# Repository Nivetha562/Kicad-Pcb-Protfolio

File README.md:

# KiCad PCB Design Portfolio

Welcome to my PCB Design Portfolio!

I am an Electronics and Communication Engineering student interested in PCB design and electronics hardware development.

## Tools Used
- KiCad
- PCB Layout Design
- Schematic Design

## My Projects

1. LED Blinker
2. PN Junction
3. Project 1.2
4. USB-C 5V Power Supply
5. Project 1.4
6. Running Light Board
7. Soil Moisture Monitoring
8. STEM Toy

## About
This repository contains my PCB design projects created using KiCad. These projects helped me improve my knowledge of electronic circuits, schematic design, and PCB layout.

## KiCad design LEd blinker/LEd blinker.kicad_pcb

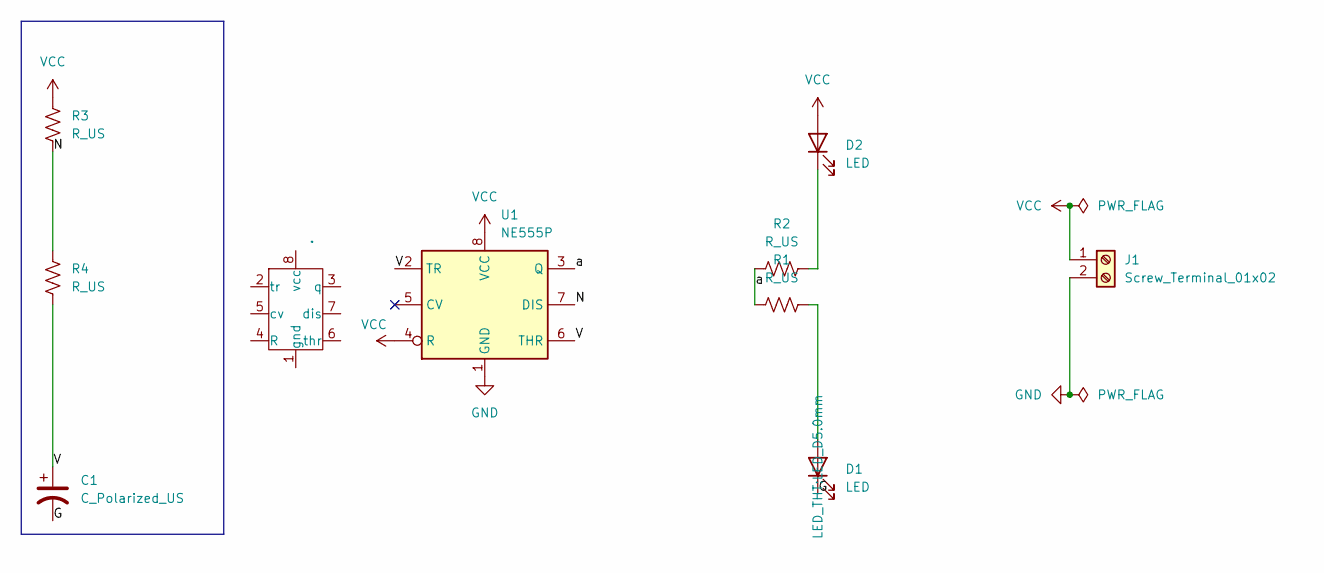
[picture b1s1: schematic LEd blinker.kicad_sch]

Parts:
C1: C_Polarized_US; CP_Axial_L11.0mm_D6.0mm_P18.00mm_Horizontal
D1, D2: LED; LED_D5.0mm
J1: Screw_Terminal_01x02; TerminalBlock_Phoenix_MKDS-1,5-2-5.08_1x02_P5.08mm_Horizont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
R1, R2: R_US; R_Axial_DIN0204_L3.6mm_D1.6mm_P7.62mm_Horizontal
R3, R4: R_US; R_Axial_DIN0207_L6.3mm_D2.5mm_P7.62mm_Horizontal
U1: NE555P; DIP-8_W7.62mm
U4: (no value)

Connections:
/G: C1.2, D1.1 (K)
/N: R3.1, R4.2, U1.7 (DIS)
/V: C1.1, R4.1, U1.2 (TR), U1.6 (THR)
/a: R1.1, R2.1, U1.3 (Q)
GND: J1.2, U1.1 (GND)
unnamed: D1.2 (A), R1.2
unnamed: D2.1 (K), R2.2
VCC: D2.2 (A), J1.1, R3.2, U1.4 (R), U1.8 (VCC)

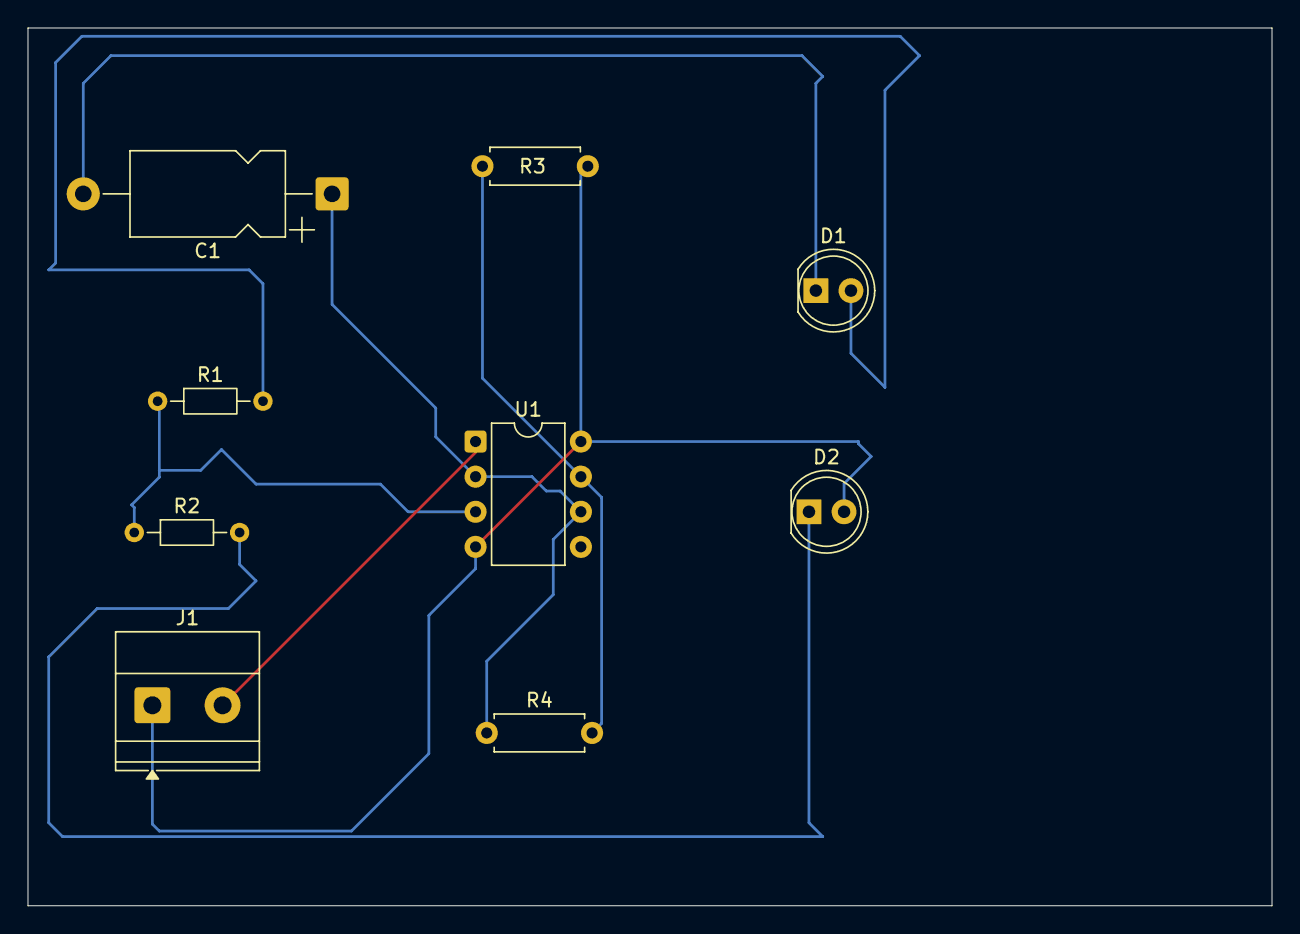
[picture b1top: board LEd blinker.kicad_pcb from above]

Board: 2 copper layers, 90.0 x 63.5 mm, 9 parts (0 on the bottom side), 8 nets.

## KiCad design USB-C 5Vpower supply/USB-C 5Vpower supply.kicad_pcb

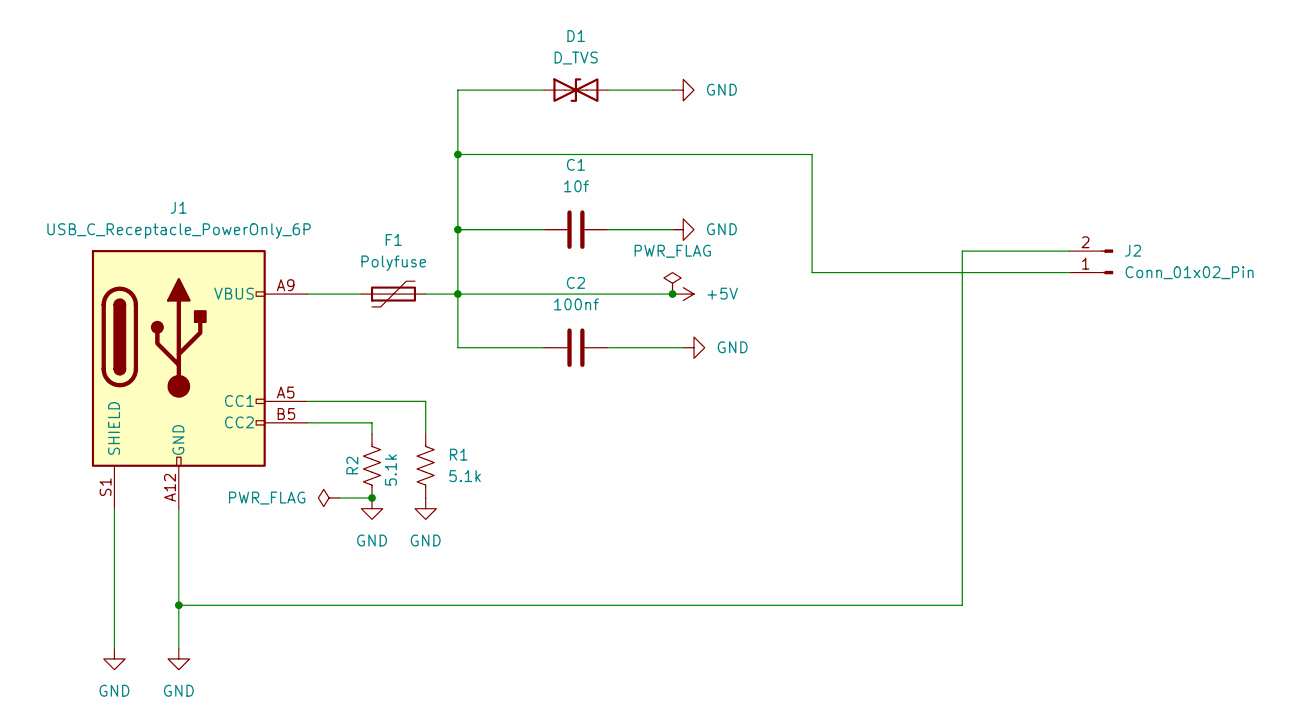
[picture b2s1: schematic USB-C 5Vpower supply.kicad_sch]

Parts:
C1: 10f; CP_Radial_D5.0mm_P2.00mm
C2: 100nf; CP_Radial_D5.0mm_P2.00mm
D1: D_TVS; D_DO-15_P5.08mm_Vertical_KathodeUp
F1: Polyfuse; Fuse_1812_4532Metric
J1: USB_C_Receptacle_PowerOnly_6P; USB_C_Receptacle_GCT_USB4125-xx-x-0190_6P_TopMnt_Horizontal
J2: Conn_01x02_Pin; SolderWire-4sqmm_1x02_P12mm_D3mm_OD6mm
R1, R2: 5.1k; R_Axial_DIN0207_L6.3mm_D2.5mm_P10.16mm_Horizontal

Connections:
+5V: C1.1, C2.1, D1.1 (A1), F1.2, J2.1
GND: C1.2, C2.2, D1.2 (A2), J1.A12 (GND), J1.B12 (GND), J1.S1 (SHIELD), J2.2, R1.2, R2.2
unnamed: F1.1, J1.A9 (VBUS), J1.B9 (VBUS)
unnamed: J1.A5 (CC1), R1.1
unnamed: J1.B5 (CC2), R2.1

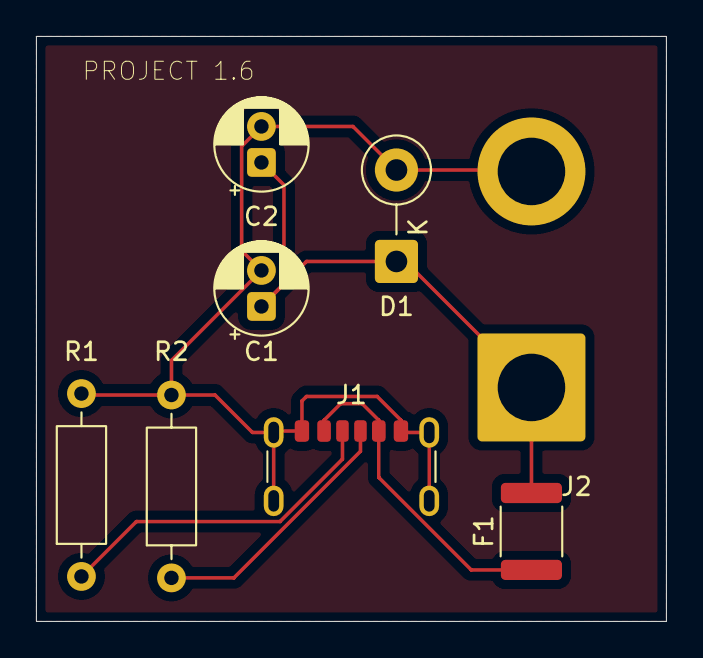
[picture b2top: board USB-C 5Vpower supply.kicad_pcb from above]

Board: 2 copper layers, 35.0 x 32.5 mm, 8 parts (0 on the bottom side), 5 nets.

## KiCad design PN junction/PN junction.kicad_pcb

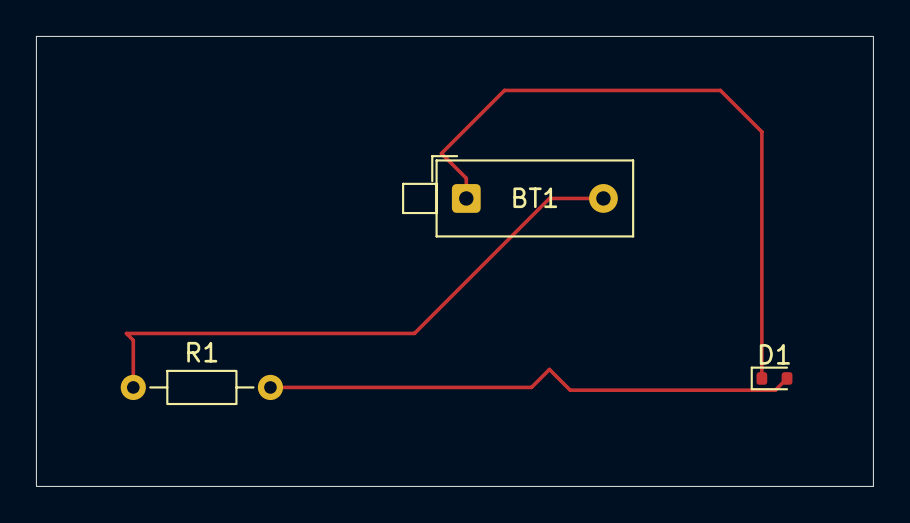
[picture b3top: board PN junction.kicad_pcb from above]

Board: 2 copper layers, 46.5 x 25.0 mm, 3 parts (0 on the bottom side), 3 nets.

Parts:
BT1: Battery_Cell; SW_DIP_SPSTx01_Piano_10.8x4.1mm_W7.62mm_P2.54mm
D1: 1N4148WT; D_SOD-523
R1: R_US; R_Axial_DIN0204_L3.6mm_D1.6mm_P7.62mm_Horizontal

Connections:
unnamed: BT1.1 (+), D1.1 (K)
unnamed: BT1.2 (-), R1.1
unnamed: D1.2 (A), R1.2

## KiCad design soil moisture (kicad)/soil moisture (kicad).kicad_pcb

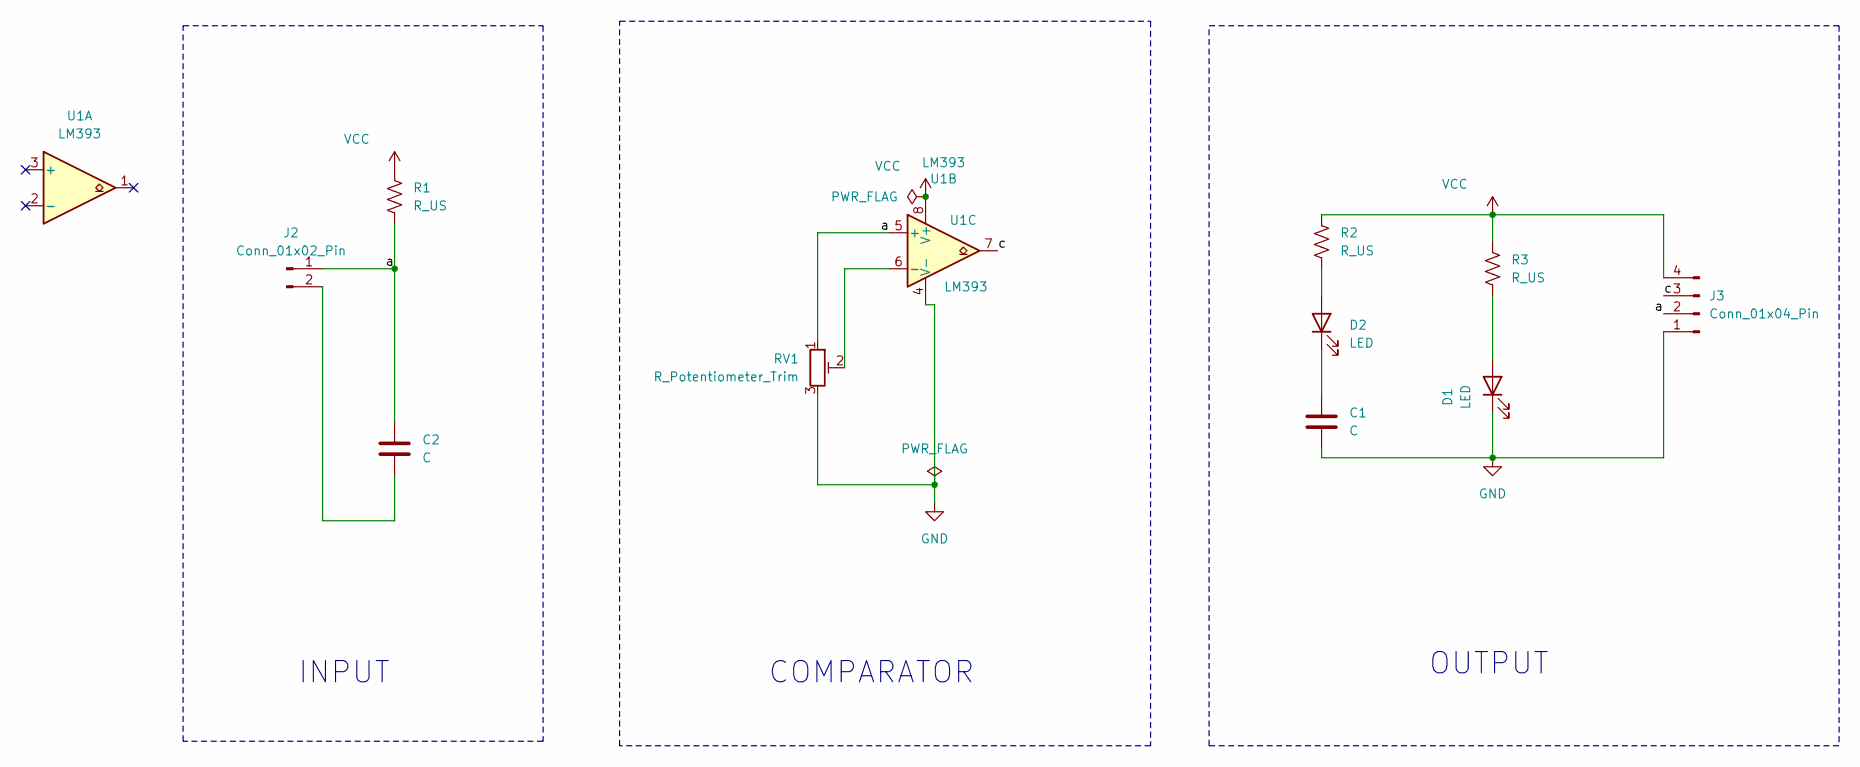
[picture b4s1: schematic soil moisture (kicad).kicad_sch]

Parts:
C1, C2: C; C_Radial_D5.0mm_H11.0mm_P2.00mm
D1, D2: LED; LED_D3.0mm_Horizontal_O1.27mm_Z2.0mm_Clear
J2: Conn_01x02_Pin; PinSocket_1x02_P2.54mm_Vertical
J3: Conn_01x04_Pin; PinSocket_1x04_P2.54mm_Vertical
R1, R2, R3: R_US; R_Axial_DIN0207_L6.3mm_D2.5mm_P15.24mm_Horizontal
RV1: R_Potentiometer_Trim; Potentiometer_Piher_PT-15-V02_Vertical
U1: LM393; DIP-8_W7.62mm

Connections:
/a: C2.1, J2.1, J3.2, R1.2, RV1.1, U1.5 (+)
/c: J3.3, U1.7
GND: C1.2, D1.1 (K), J3.1, RV1.3, U1.4 (V-)
unnamed: D1.2 (A), R3.2
unnamed: D2.2 (A), R2.2
unnamed: C1.1, D2.1 (K)
unnamed: C2.2, J2.2
unnamed: RV1.2, U1.6 (-)
VCC: J3.4, R1.1, R2.1, R3.1, U1.8 (V+)

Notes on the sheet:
OUTPUT
COMPARATOR
INPUT

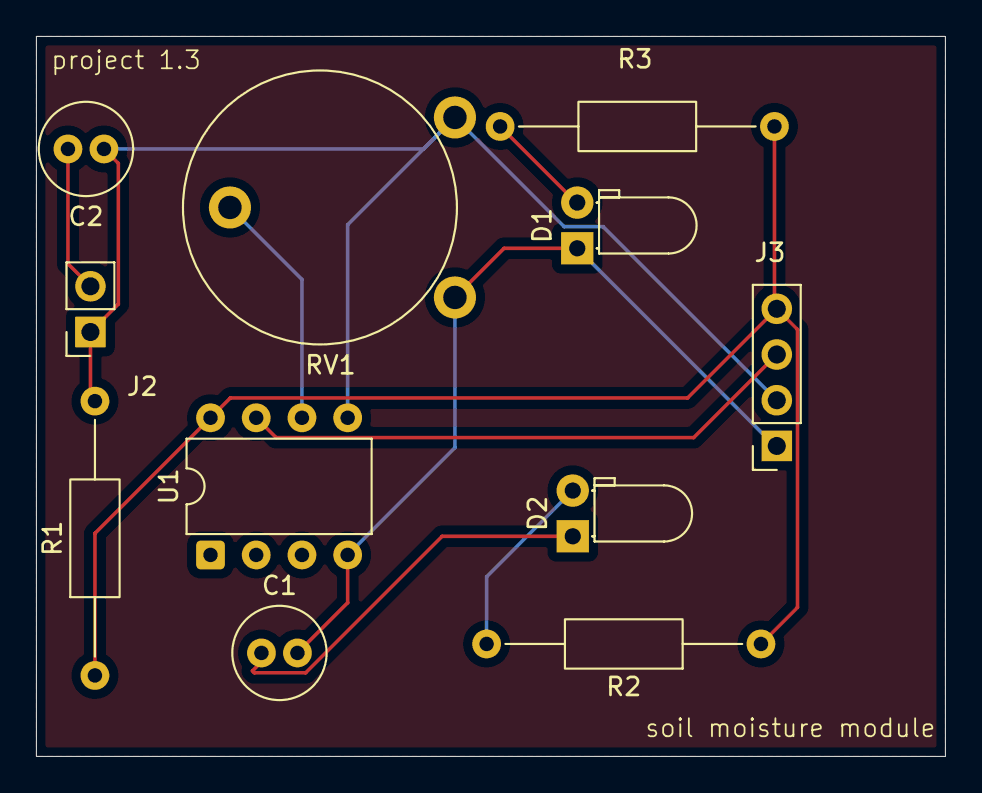
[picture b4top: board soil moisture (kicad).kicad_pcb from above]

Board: 2 copper layers, 50.5 x 40.0 mm, 11 parts (0 on the bottom side), 9 nets.

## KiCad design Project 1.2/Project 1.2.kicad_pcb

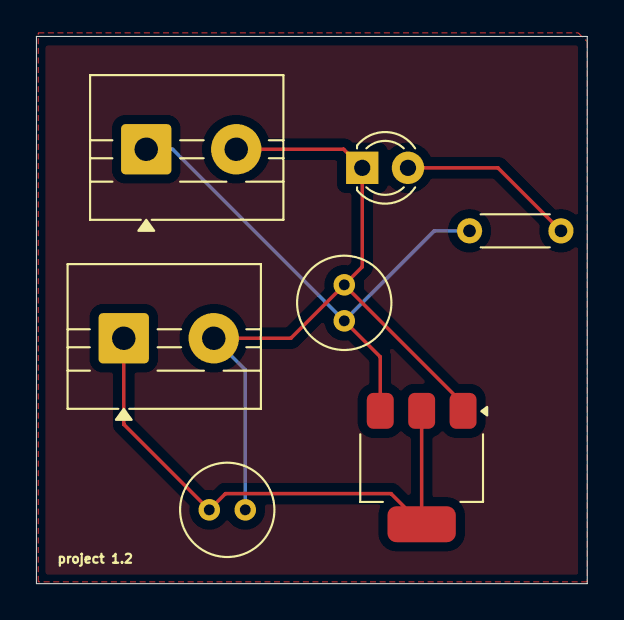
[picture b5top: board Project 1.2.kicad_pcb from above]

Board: 2 copper layers, 30.6 x 30.4 mm, 7 parts (0 on the bottom side), 4 nets.

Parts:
C1, C2: C; C_Radial_D5.0mm_H5.0mm_P2.00mm
D1: LED; LED_D3.0mm
J1: 5v input; TerminalBlock_MaiXu_MX126-5.0-02P_1x02_P5.00mm
J2: 3.3v output; TerminalBlock_MaiXu_MX126-5.0-02P_1x02_P5.00mm
R2: R; R_Axial_DIN0204_L3.6mm_D1.6mm_P5.08mm_Horizontal
U1: AMS1117-3.3; SOT-223-3_TabPin2

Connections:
/a: C2.1, J2.1, U1.2 (VO)
/b: C1.1, J1.1, R2.1, U1.3 (VI)
/gnd: C1.2, C2.2, D1.1 (K), J1.2, J2.2, U1.1 (GND)
unnamed: D1.2 (A), R2.2

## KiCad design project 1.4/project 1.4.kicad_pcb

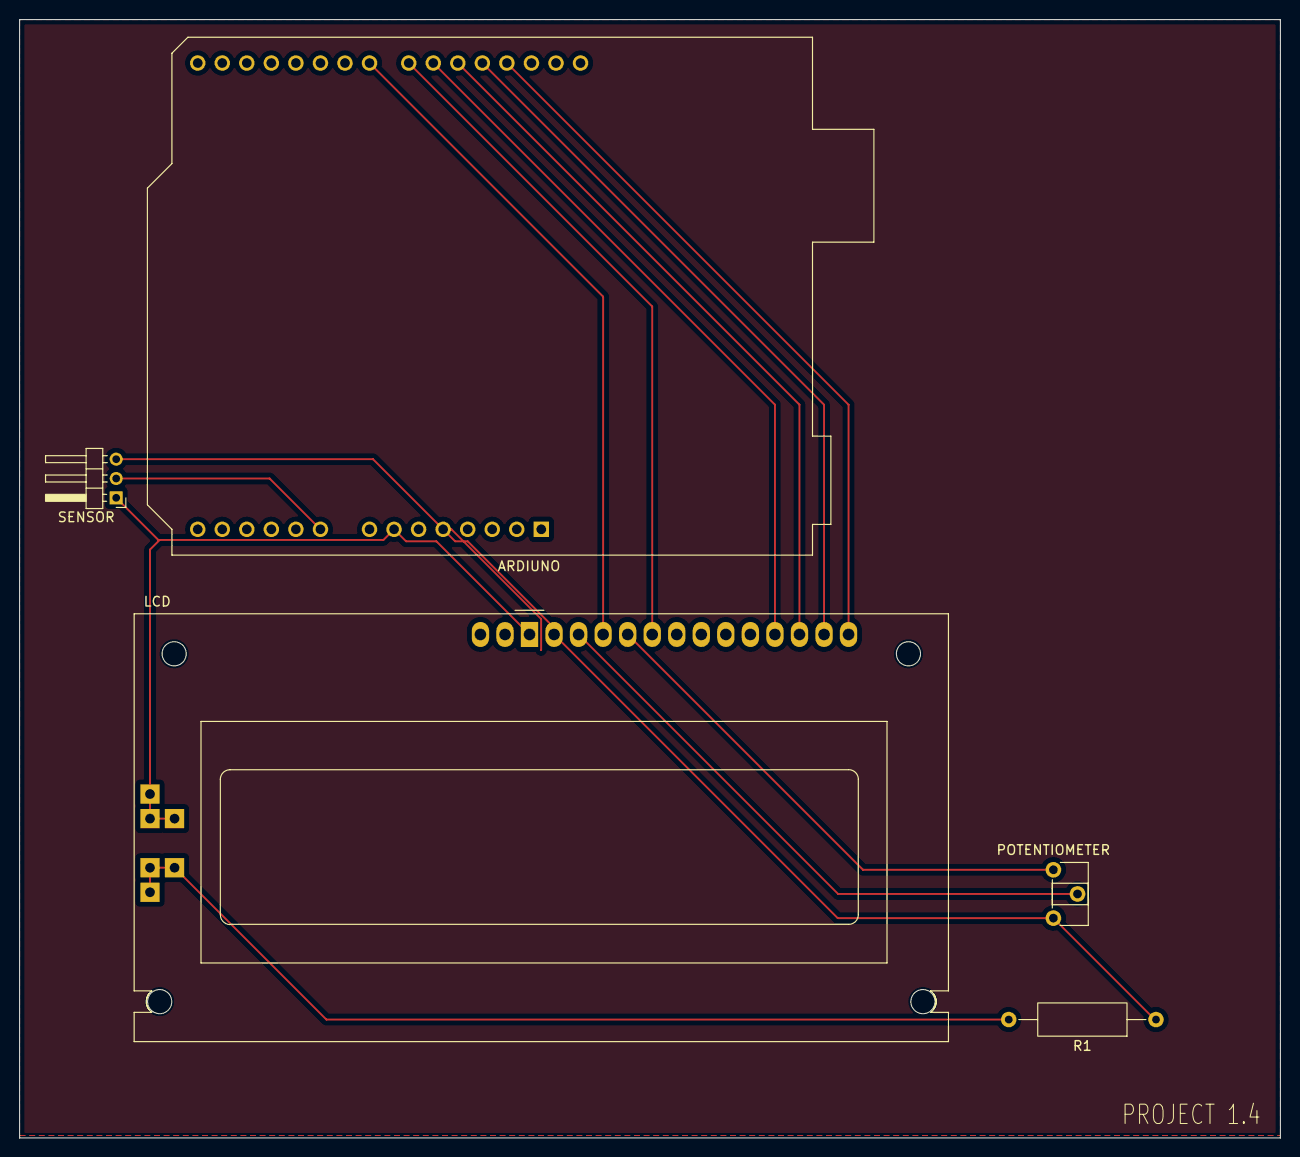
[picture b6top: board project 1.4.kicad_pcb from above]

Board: 2 copper layers, 130.5 x 115.8 mm, 5 parts (0 on the bottom side), 12 nets.

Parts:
ARDIUNO: Arduino_UNO; Arduino_UNO_R2
LCD: LCD DISPLAY; RC1602A
POTENTIOMETER: R_Potentiometer; Potentiometer_ACP_CA6-H2,5_Horizontal
R1: RESISTOR; R_Axial_DIN0309_L9.0mm_D3.2mm_P15.24mm_Horizontal
SENSOR: SOIL MOISTURE SENSOR; PinHeader_1x03_P2.00mm_Horizontal

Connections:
/5V: ARDIUNO.5 (+5V), LCD.2 (VDD), POTENTIOMETER.3, R1.1, SENSOR.3
/A: ARDIUNO.9 (A0), SENSOR.2
/IN: ARDIUNO.7 (GND), LCD.1 (VSS), LCD.K1 (K), SENSOR.1
/V0: LCD.3 (Vo), POTENTIOMETER.2
/b: ARDIUNO.22 (D7), LCD.4 (RS)
/c: ARDIUNO.23 (D8), LCD.6 (~E)
/d: ARDIUNO.24 (D9), LCD.11 (DB4)
/e: ARDIUNO.25 (D10), LCD.12 (DB5)
/f: ARDIUNO.26 (D11), LCD.13 (DB6)
/g: ARDIUNO.27 (D12), LCD.14 (DB7)
GND: LCD.5 (R/~W), POTENTIOMETER.1
unnamed: LCD.A1 (A), R1.2

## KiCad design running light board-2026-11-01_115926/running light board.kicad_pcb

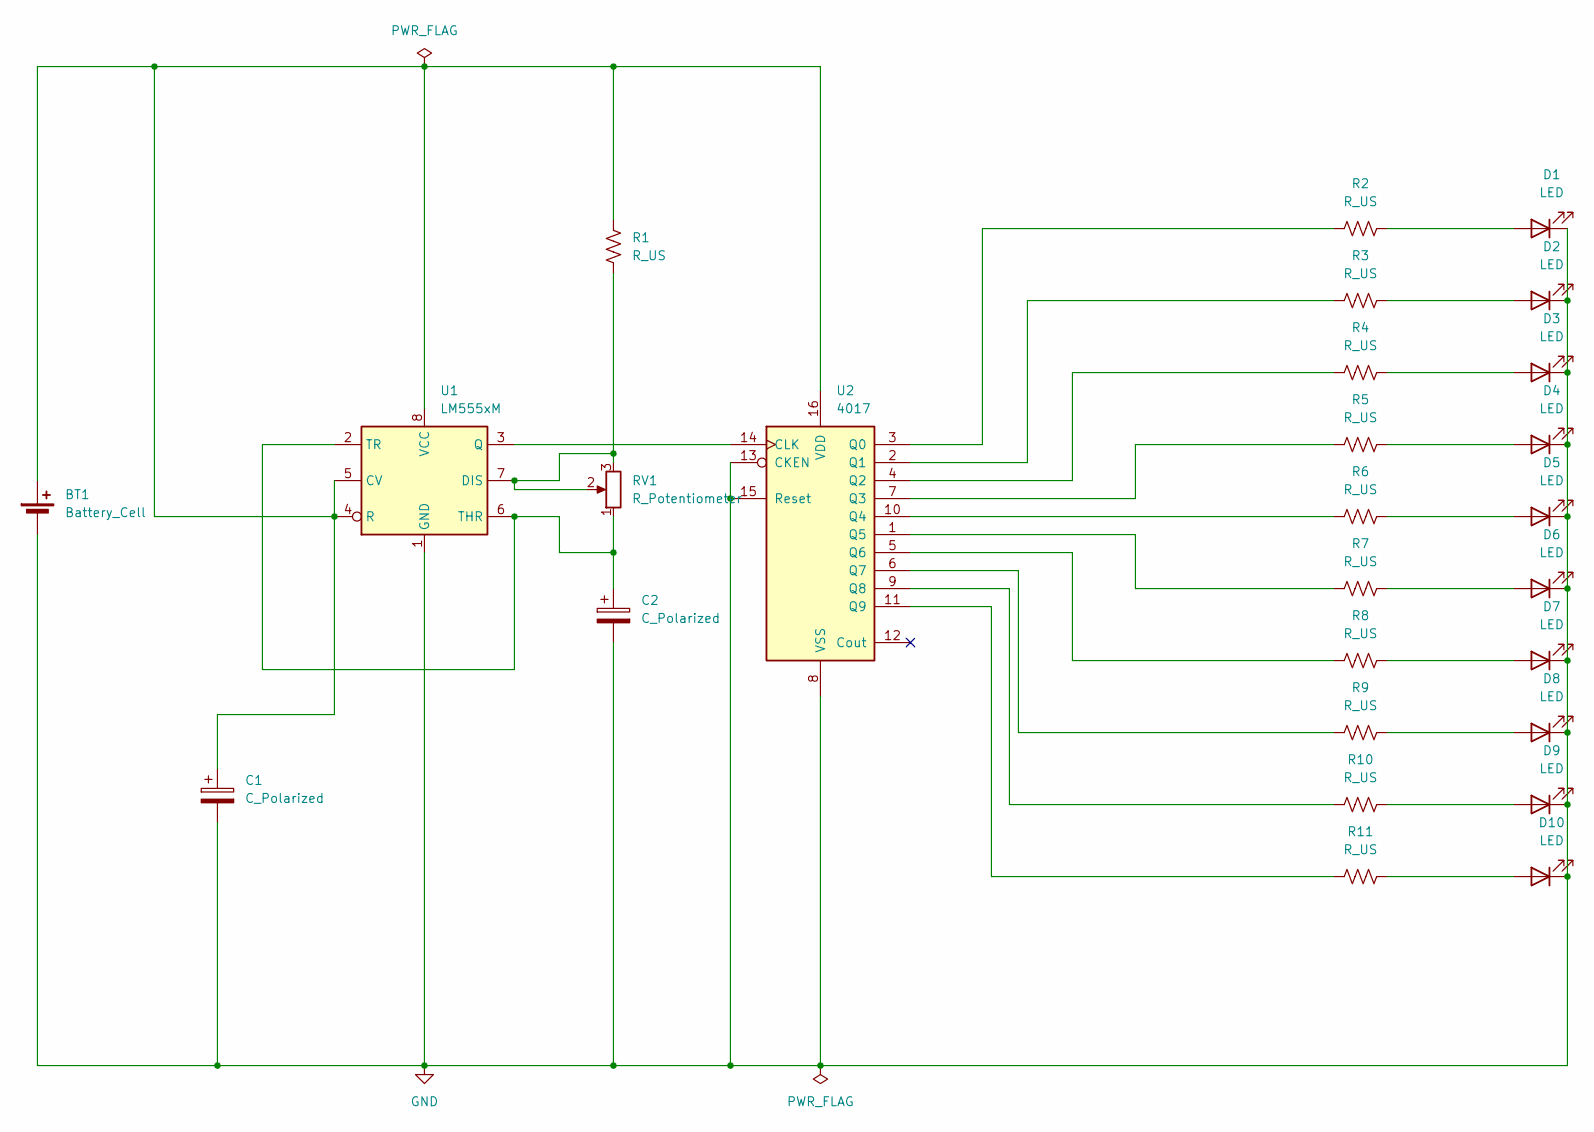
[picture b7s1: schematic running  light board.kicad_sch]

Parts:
BT1: Battery_Cell; TerminalBlock_Phoenix_MKDS-1,5-2_1x02_P5.00mm_Horizontal
C1, C2: C_Polarized; CP_Radial_Tantal_D5.0mm_P2.50mm
D1, D2, D3, D4, D5, D6, D7, D8, D9, D10: LED; LED_D3.0mm
R1, R2, R3, R4, R5, R6, R7, R8, R9, R10, R11: R_US; R_Axial_DIN0204_L3.6mm_D1.6mm_P7.62mm_Horizontal
RV1: R_Potentiometer; Potentiometer_Bourns_3339P_Vertical
U1: LM555xM; DIP-8_W7.62mm
U2: 4017; DIP-16_W7.62mm

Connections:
GND: BT1.2 (-), C1.2, C2.2, D1.1 (K), D2.1 (K), D3.1 (K), D4.1 (K), D5.1 (K), D6.1 (K), D7.1 (K), D8.1 (K), D9.1 (K), D10.1 (K), U1.1 (GND), U2.8 (VSS), U2.13 (CKEN), U2.15 (Reset)
unnamed: BT1.1 (+), C1.1, R1.1, U1.4 (R), U1.5 (CV), U1.8 (VCC), U2.16 (VDD)
unnamed: D1.2 (A), R2.2
unnamed: D2.2 (A), R3.2
unnamed: D3.2 (A), R4.2
unnamed: D4.2 (A), R5.2
unnamed: D5.2 (A), R6.2
unnamed: D6.2 (A), R7.2
unnamed: D7.2 (A), R8.2
unnamed: D8.2 (A), R9.2
unnamed: D9.2 (A), R10.2
unnamed: D10.2 (A), R11.2
unnamed: R1.2, RV1.2, RV1.3, U1.7 (DIS)
unnamed: U1.3 (Q), U2.14 (CLK)
unnamed: C2.1, RV1.1, U1.2 (TR), U1.6 (THR)
unnamed: R2.1, U2.3 (Q0)
unnamed: R3.1, U2.2 (Q1)
unnamed: R4.1, U2.4 (Q2)
unnamed: R5.1, U2.7 (Q3)
unnamed: R6.1, U2.10 (Q4)
unnamed: R7.1, U2.1 (Q5)
unnamed: R8.1, U2.5 (Q6)
unnamed: R9.1, U2.6 (Q7)
unnamed: R10.1, U2.9 (Q8)
unnamed: R11.1, U2.11 (Q9)

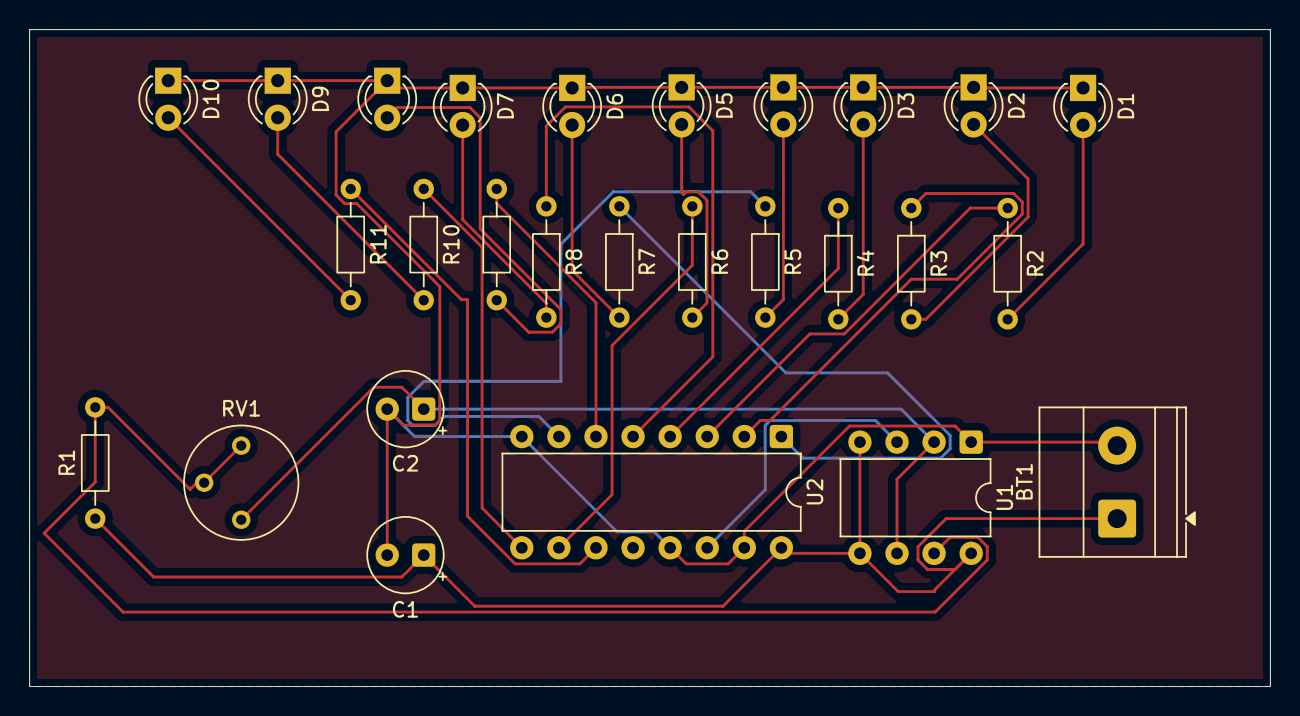
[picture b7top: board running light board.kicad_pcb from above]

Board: 2 copper layers, 85.0 x 45.0 mm, 27 parts (0 on the bottom side), 25 nets.

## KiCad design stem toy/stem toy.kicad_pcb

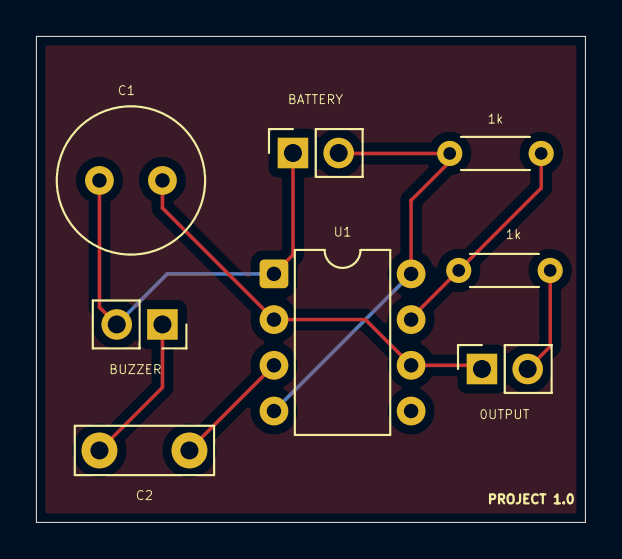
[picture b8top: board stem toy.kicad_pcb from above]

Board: 2 copper layers, 30.5 x 27.0 mm, 8 parts (0 on the bottom side), 7 nets.

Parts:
0UTPUT: HUMANS; PinSocket_1x02_P2.54mm_Vertical
1k, 1k#2: R; R_Axial_DIN0204_L3.6mm_D1.6mm_P5.08mm_Horizontal
BATTERY: BATTERY; PinSocket_1x02_P2.54mm_Vertical
BUZZER: BUZZER; PinSocket_1x02_P2.54mm_Vertical
C1: C; C_Radial_D8.0mm_H11.5mm_P3.50mm
C2: C_Polarized; C_Disc_D7.5mm_W2.5mm_P5.00mm
U1: NE555P; DIP-8_W7.62mm

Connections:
/OUTPUT: C2.1, U1.3 (Q)
/Q1: 1k.2, 1k#2.1, U1.7 (DIS)
/Q2: 0UTPUT.1, C1.2, U1.2 (TR), U1.6 (THR)
GND: BATTERY.1, BUZZER.2, C1.1, U1.1 (GND)
unnamed: BUZZER.1, C2.2
unnamed: 0UTPUT.2, 1k#2.2
VCC: 1k.1, BATTERY.2, U1.4 (R), U1.8 (VCC)
